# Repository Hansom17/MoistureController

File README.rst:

.. zephyr:code-sample:: moisture-controller
   :name: Moisture Controller

   Print "Hello World" to the console.

Overview
********

A simple sample that can be used with any :ref:`supported board <boards>` and
prints "Hello World" to the console.

Building and Running
********************

This application can be built and executed on QEMU as follows:

.. zephyr-app-commands::
   :zephyr-app: samples/hello_world
   :host-os: unix
   :board: qemu_x86
   :goals: run
   :compact:

To build for another board, change "qemu_x86" above to that board's name.

Sample Output
=============

.. code-block:: console

    Hello World! x86

Exit QEMU by pressing :kbd:`CTRL+A` :kbd:`x`.

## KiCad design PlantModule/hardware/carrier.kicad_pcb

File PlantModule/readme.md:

# PlantModule

Plant device: an ESP32-C6 Zigbee end device, always awake for now (low power comes later). Design: [`specs.md`](specs.md).

```
firmware/    ESP-IDF project (build and flash: see below): main/, components/{mc_core,mc_hal,mc_zigbee}; host tests in firmware/test
hardware/    KiCad carrier board for the Waveshare ESP32-C6-Zero (specs.md Part C)
interface.yaml   the Zigbee interface definition (source for firmware header, converter and hub models)
scripts/     qr_png.swift (QR image for labels); the provisioning/label tool (make_label.py) is to be written
```

**State:** carrier board v1 is built and in hand; the firmware (host-tested core, hardware layer, esp-zigbee-sdk layer) builds, runs on the bench module and works with Zigbee2MQTT and the gateway (join, configuration, readings, watering, battery detection). Not done: provisioning (`make_label.py`, factory data, install codes), low power, a real battery cell test. The previous Zephyr/WiFi/MQTT/BLE firmware and its tests were removed and are in git history at commit `eb97b07`.

## Hardware

Regenerate and order from `hardware/`: `gen_sch.py` (schematic), `gen_pcb.py` (needs KiCad's bundled Python), `jlc_export.py` (JLCPCB files). `design.py` is the single source. Details and status in Part C of the spec.

## Build and flash the firmware

Needs **ESP-IDF v6.0.2** (installed with Espressif's installer; `~/.espressif/v6.0.2`), a USB cable to the module's USB-C port and, to see anything useful, a Zigbee coordinator with Zigbee2MQTT (the gateway, or `Gateway/scripts/bench.sh`).

### 1. Set up the shell (once per terminal)

```bash
source ~/.espressif/tools/activate_idf_v6.0.2.sh
cd PlantModule/firmware
```

### 2. Build

For a **bench module** (no factory data yet: it runs as the `carrier-v1` board and joins with the default Zigbee link key):

```bash
rm -f sdkconfig        # only when you switch between a bench and a release configuration
idf.py -DSDKCONFIG_DEFAULTS="sdkconfig.defaults;sdkconfig.dev" build
```

For a **release build** (no dev options; a module without valid factory data then enters safe mode, which is intended):

```bash
idf.py build
```

The target (ESP32-C6) is in `sdkconfig.defaults`, no `set-target` is needed. The first build downloads the Zigbee components (`espressif/esp-zigbee-lib`, `esp-zboss-lib`, pinned in `dependencies.lock`). Other options are in `idf.py menuconfig` under "PlantModule" and "PlantModule Zigbee": the development board and join flag, `CONFIG_MC_ZB_TX_POWER` (default 10 dBm) and `CONFIG_MC_ZIGBEE_STUB` (log instead of radio, for bench tests without a coordinator).

If the build stops with "build log version is too new" or a `build.ninja` error, the `build/` folder came from another ninja version: `idf.py fullclean`, then build again.

### 3. Find the module's port

```bash
ls /dev/cu.usb*          # macOS; Linux: ls /dev/ttyACM*
```

The ESP32-C6 shows up as `usbmodem…` (macOS) or `ttyACM…` (Linux). A Zigbee dongle shows up as `usbserial…`: do **not** flash that. The name changes when you use another USB port.

### 4. Flash

```bash
idf.py -p /dev/cu.usbmodem1101 flash
```

That writes the bootloader, the partition table and the app and **keeps the settings and the Zigbee network** (NVS and `zb_storage` are not touched). For a faster app-only update:

```bash
python -m esptool --port /dev/cu.usbmodem1101 write-flash 0x20000 build/plantmodule.bin
```

### Flashing all partitions (a new module, or a clean start)

`idf.py flash` writes the bootloader, the partition table, OTA data and the app. The **data partitions** are not written: `nvs` (settings, counters), `factory` (board name, serial, install code) and the Zigbee storage `zb_storage`/`zb_fct`. The layout is in `firmware/partitions.csv`:

| Partition | Offset | Size | Written by |
|---|---|---|---|
| bootloader | `0x0` | | `idf.py flash` |
| partition table | `0x8000` | | `idf.py flash` |
| `nvs` | `0x9000` | `0x6000` | the firmware at run time |
| `otadata` | `0xf000` | `0x2000` | `idf.py flash` |
| `phy_init` | `0x11000` | `0x1000` | the firmware at run time |
| `factory` | `0x12000` | `0x1000` | **`scripts/factory_image.py`, below** |
| `zb_storage`, `zb_fct` | `0x13000`, `0x17000` | `0x4000`, `0x1000` | the Zigbee stack at run time |
| `ota_0` (the app) | `0x20000` | `0x1a0000` | `idf.py flash` |

**A module from scratch** (all partitions, including the factory data):

```bash
python -m esptool --port /dev/cu.usbmodem1101 erase-flash                      # wipes everything, also the factory data
../scripts/factory_image.py --board carrier-v1 --serial MC000001 --out factory.bin
idf.py -p /dev/cu.usbmodem1101 flash                                           # bootloader, table, otadata, app
python -m esptool --port /dev/cu.usbmodem1101 write-flash 0x12000 factory.bin # the factory partition
```

`scripts/factory_image.py` builds the 4 KB image of the `factory` partition (layout in `specs.md` §10 and `mc_factory.h`; the C parser accepts what it writes). Add `--install-code <32 hex characters>` for a module that must use an install code and `--require-install-code` so that it refuses to join without one. Keep the install code and the image out of git: the code is a secret, and the gateway needs the same code to accept the module.

Without factory data a module enters safe mode (`factory_invalid`), unless it is a bench build (`sdkconfig.dev`), which runs as `carrier-v1`. A module with factory data is not touched by a normal `idf.py flash`, and a factory reset (10 s button) keeps it.

**One file** (for a production line, or to flash from another machine that has no ESP-IDF):

```bash
idf.py merge-bin                       # build/merged-binary.bin: bootloader, table, otadata and app in one image
python -m esptool --port /dev/cu.usbmodem1101 write-flash 0x0 build/merged-binary.bin
python -m esptool --port /dev/cu.usbmodem1101 write-flash 0x12000 factory.bin     # then the factory data
```

The merged image **fills the gaps between its parts with `0xFF`**, so writing it also **erases `nvs`, `factory` and the Zigbee storage**: the module forgets its settings and its network, and the factory data must be written again afterwards (the last line). Use it only for a clean start, never as an update of a module in use.

### 5. Look at the log

```bash
idf.py -p /dev/cu.usbmodem1101 monitor     # Ctrl+] leaves
```

**Opening the USB port of the C6 resets the module** (most serial tools do). That is harmless, but a module that is working would restart and rejoin. The log shows `boot reason`, `stack ready, joined` or `factory new`, and the Zigbee signals.

### 6. Join the module to the gateway

1. Open the join window (app: **Devices → Add device**).
2. A module that has never joined starts looking for a network by itself (fast LED blink, about three minutes). One that belonged to another network: **hold the button for 10 seconds** (factory reset), it restarts and looks for a network. A short press only identifies it (LED blinks); a 3 s hold starts a search when it is not joined.
3. The module appears in the app (joined, interview, configure, ready); set its slots in **Edit configuration**.

### Changing the attribute set

Adding, removing or re-ordering attributes in `interface.yaml` (or editing its `reporting` table) needs **no erase and no new join**. The Zigbee stack keeps its reporting records in `zb_storage` and with records left over from a different attribute set it aborts at the first report (`zb_assert`). So the firmware hashes what it registers and remembers the hash in NVS (`mc_zb/attr_hash`). On the first start after a change it throws the stored records away and sets up its own from the `reporting` table (log line `attribute set changed: reporting records rebuilt`); the network, the bindings and the settings stay. A module without a network just stores the new hash. Flash the app only (`write-flash 0x20000 build/plantmodule.bin`) and the module comes back on its own.

The Zigbee storage still has to be erased for a module whose network is gone (new coordinator) or to start from scratch:

```bash
python -m esptool --port /dev/cu.usbmodem1101 erase-region 0x9000 0x6000     # NVS: settings, counters, "has booted" flag
python -m esptool --port /dev/cu.usbmodem1101 erase-region 0x13000 0x5000    # Zigbee storage and its factory-test partition
```

Then open the join window, wait for the module, and the gateway's configure step runs again.

### Changing a value of the interface

Values in `interface.yaml` (ranges, defaults, battery tunables) are compiled into the firmware; after editing it regenerate and rebuild:

```bash
python3 scripts/gen_interface_h.py && python3 ../Gateway/scripts/gen_converter.py && python3 ../Gateway/scripts/gen_hub_params.py
```

Not everything needs a flash: the table in `specs.md` §6.1 shows for each battery setting whether the module, the hub or both use it. Hub-only values (the percentage curve) need only the regenerate step and a hub restart; thresholds and calibration are set from the app and need no rebuild.

### Tests (no hardware, no ESP-IDF)

```bash
scripts/test_host.sh       # generated files are current, then the 127 host tests with ASan/UBSan
```

CI runs this on every pull request and also builds the firmware for the ESP32-C6 (`firmware-build` job in `.github/workflows/ci.yml`).

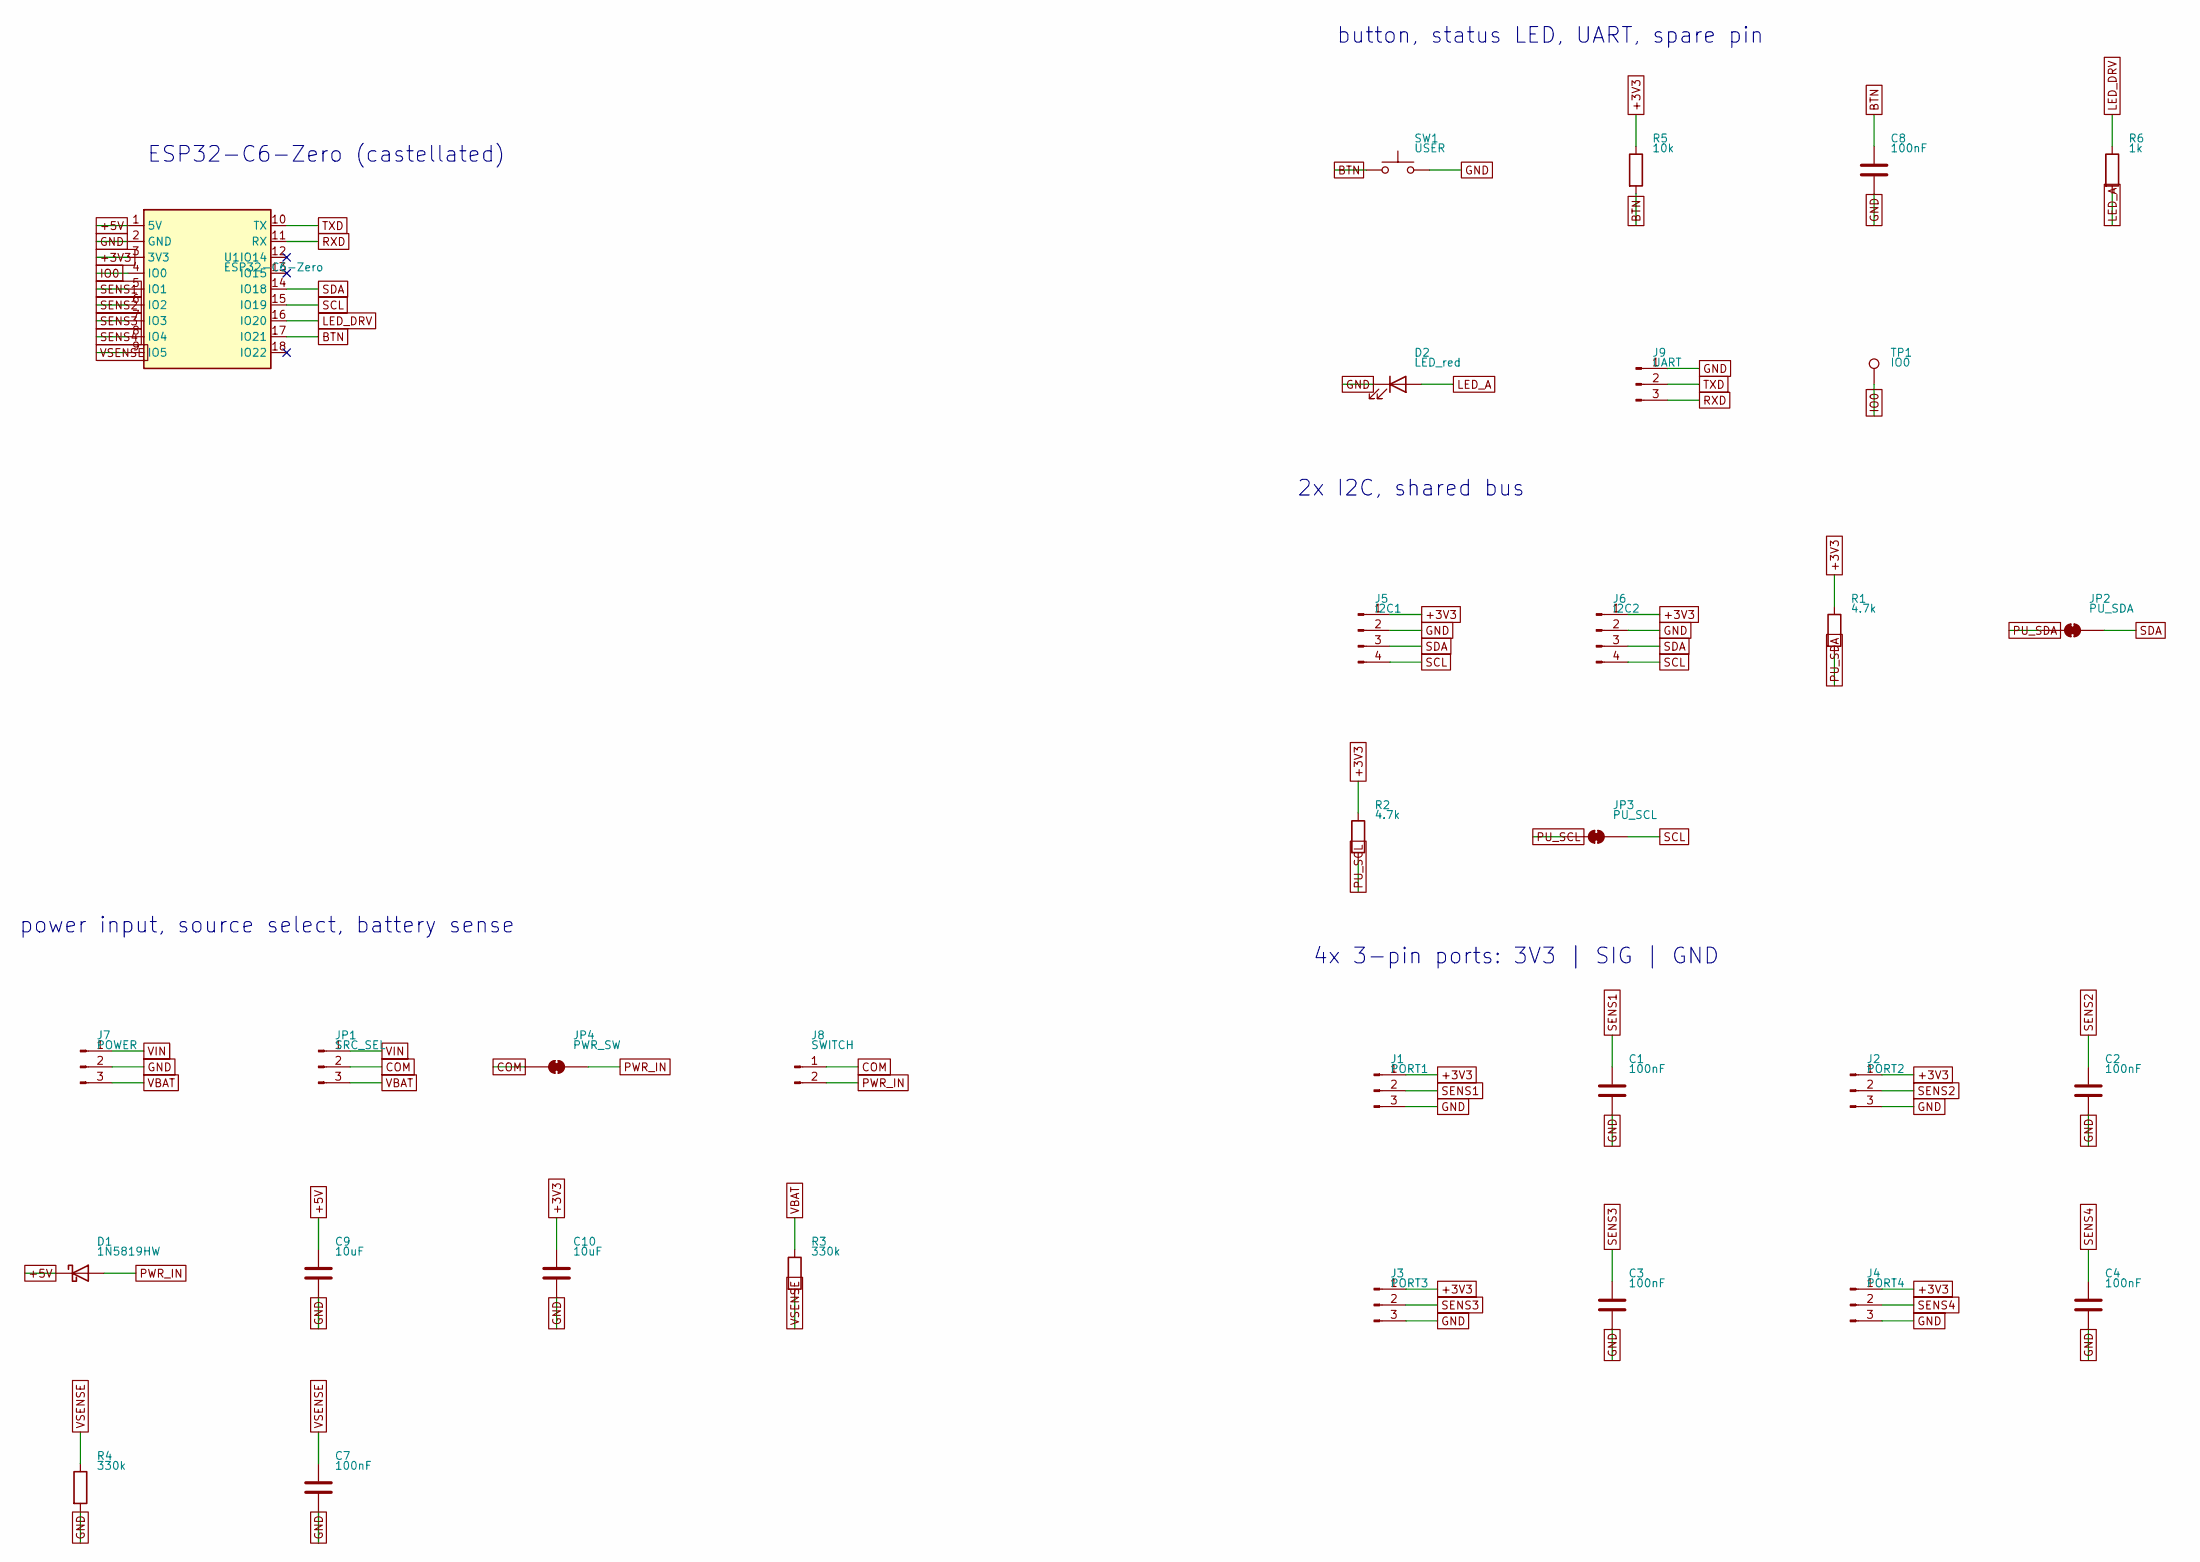
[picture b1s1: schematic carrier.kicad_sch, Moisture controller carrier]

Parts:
C1, C2, C3, C4, C7, C8: 100nF; C_0603_1608Metric
C9, C10: 10uF; C_0805_2012Metric
D1: 1N5819HW; D_SOD-123
D2: LED_red; LED_0603_1608Metric
J1: PORT1; JST_XH_B3B-XH-A_1x03_P2.50mm_Vertical
J2: PORT2; JST_XH_B3B-XH-A_1x03_P2.50mm_Vertical
J3: PORT3; JST_XH_B3B-XH-A_1x03_P2.50mm_Vertical
J4: PORT4; JST_XH_B3B-XH-A_1x03_P2.50mm_Vertical
J5: I2C1; JST_XH_B4B-XH-A_1x04_P2.50mm_Vertical
J6: I2C2; JST_XH_B4B-XH-A_1x04_P2.50mm_Vertical
J7: POWER; JST_XH_B3B-XH-A_1x03_P2.50mm_Vertical
J8: SWITCH; PinHeader_1x02_P2.54mm_Vertical
J9: UART; PinHeader_1x03_P2.54mm_Vertical
JP1: SRC_SEL; PinHeader_1x03_P2.54mm_Vertical
JP2: PU_SDA; SolderJumper-2_P1.3mm_Bridged_RoundedPad1.0x1.5mm
JP3: PU_SCL; SolderJumper-2_P1.3mm_Bridged_RoundedPad1.0x1.5mm
JP4: PWR_SW; SolderJumper-2_P1.3mm_Bridged_RoundedPad1.0x1.5mm
R1, R2: 4.7k; R_0603_1608Metric
R3, R4: 330k; R_0603_1608Metric
R5: 10k; R_0603_1608Metric
R6: 1k; R_0603_1608Metric
SW1: USER; SW_Push_1P1T_NO_CK_KMR2
TP1: IO0; TestPoint_Pad_D1.5mm
U1: ESP32-C6-Zero

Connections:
+3V3: C10.1, J1.1, J2.1, J3.1, J4.1, J5.1, J6.1, R1.1, R2.1, R5.1, U1.3 (3V3)
+5V: C9.1, D1.1 (K), U1.1 (5V)
BTN: C8.1, R5.2, SW1.1, U1.17 (IO21)
COM: J8.1, JP1.2, JP4.1 (A)
GND: C1.2, C2.2, C3.2, C4.2, C7.2, C8.2, C9.2, C10.2, D2.1 (K), J1.3, J2.3, J3.3, J4.3, J5.2, J6.2, J7.2, J9.1, R4.2, SW1.2, U1.2 (GND)
IO0: TP1.1 (1_1), U1.4 (IO0)
LED_A: D2.2 (A), R6.2
LED_DRV: R6.1, U1.16 (IO20)
PU_SCL: JP3.1 (A), R2.2
PU_SDA: JP2.1 (A), R1.2
PWR_IN: D1.2 (A), J8.2, JP4.2 (B)
RXD: J9.3, U1.11 (RX)
SCL: J5.4, J6.4, JP3.2 (B), U1.15 (IO19)
SDA: J5.3, J6.3, JP2.2 (B), U1.14 (IO18)
SENS1: C1.1, J1.2, U1.5 (IO1)
SENS2: C2.1, J2.2, U1.6 (IO2)
SENS3: C3.1, J3.2, U1.7 (IO3)
SENS4: C4.1, J4.2, U1.8 (IO4)
TXD: J9.2, U1.10 (TX)
VBAT: J7.3, JP1.3, R3.1
VIN: J7.1, JP1.1
VSENSE: C7.1, R3.2, R4.1, U1.9 (IO5)

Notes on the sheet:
button, status LED, UART, spare pin
ESP32-C6-Zero (castellated)
power input, source select, battery sense
2x I2C, shared bus
4x 3-pin ports: 3V3 | SIG | GND

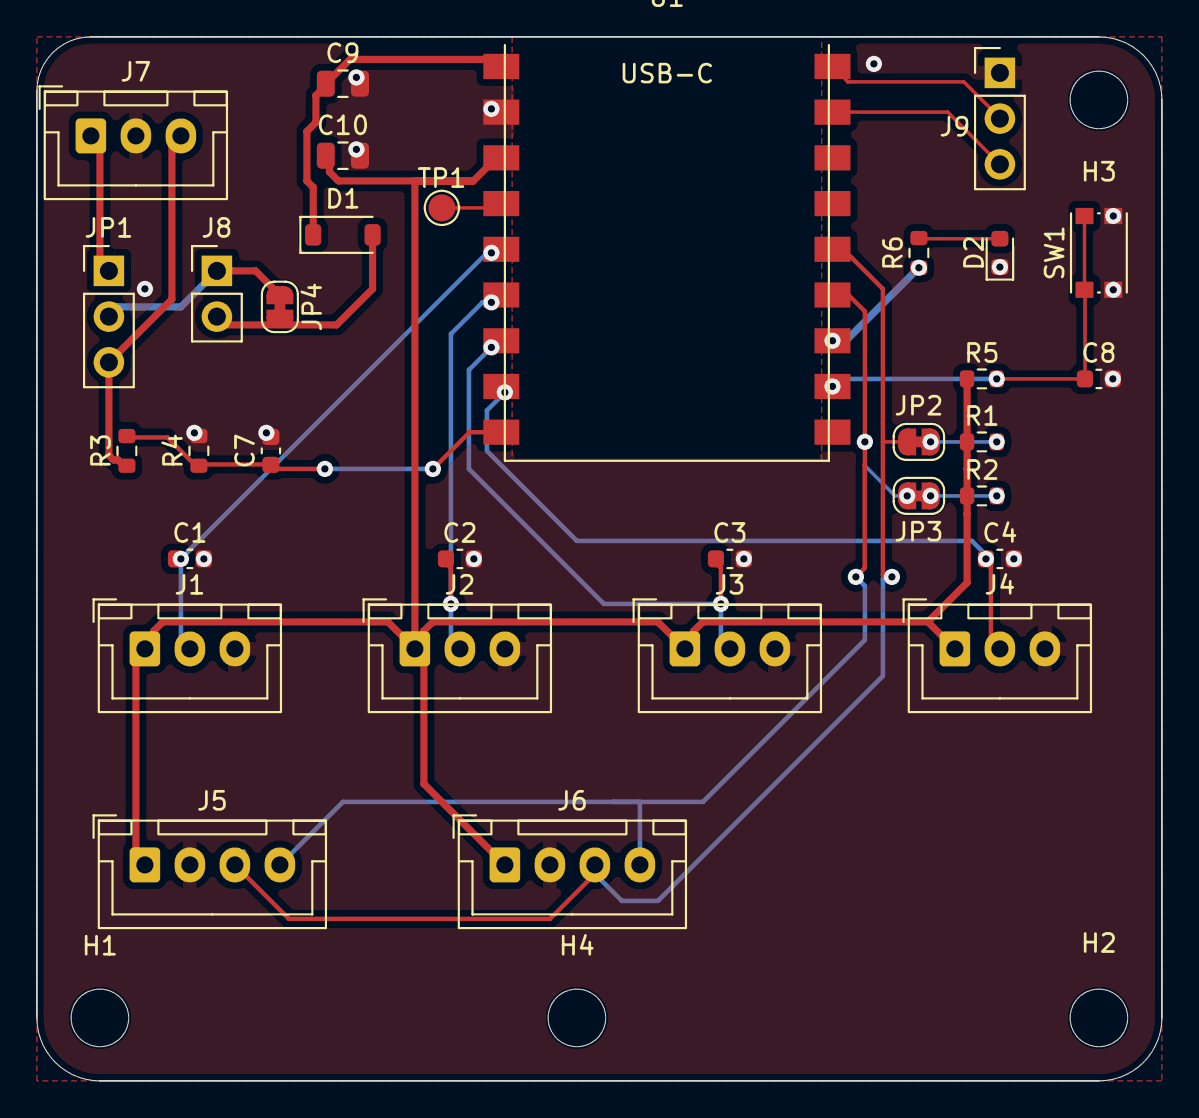
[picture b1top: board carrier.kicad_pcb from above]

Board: 2 copper layers, 62.5 x 58.0 mm, 36 parts (0 on the bottom side), 22 nets.

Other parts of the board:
H1, H2, H3, H4: M3; MountingHole_3.2mm_M3

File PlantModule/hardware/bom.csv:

"Refs","Value","Footprint","Qty"
"C1-C4,C7,C8","100nF","Capacitor_SMD:C_0603_1608Metric","6"
"C9,C10","10uF","Capacitor_SMD:C_0805_2012Metric","2"
"D1","B5819W","Diode_SMD:D_SOD-123","1"
"D2","STATUS","LED_SMD:LED_0603_1608Metric","1"
"J1","PORT1","Connector_JST:JST_XH_B3B-XH-A_1x03_P2.50mm_Vertical","1"
"J2","PORT2","Connector_JST:JST_XH_B3B-XH-A_1x03_P2.50mm_Vertical","1"
"J3","PORT3","Connector_JST:JST_XH_B3B-XH-A_1x03_P2.50mm_Vertical","1"
"J4","PORT4","Connector_JST:JST_XH_B3B-XH-A_1x03_P2.50mm_Vertical","1"
"J5","I2C1","Connector_JST:JST_XH_B4B-XH-A_1x04_P2.50mm_Vertical","1"
"J6","I2C2","Connector_JST:JST_XH_B4B-XH-A_1x04_P2.50mm_Vertical","1"
"J7","POWER","Connector_JST:JST_XH_B3B-XH-A_1x03_P2.50mm_Vertical","1"
"J8","SWITCH","Connector_PinHeader_2.54mm:PinHeader_1x02_P2.54mm_Vertical","1"
"J9","UART","Connector_PinHeader_2.54mm:PinHeader_1x03_P2.54mm_Vertical","1"
"JP1","SRC_SEL","Connector_PinHeader_2.54mm:PinHeader_1x03_P2.54mm_Vertical","1"
"R1,R2","4.7k","Resistor_SMD:R_0603_1608Metric","2"
"R3,R4","330k","Resistor_SMD:R_0603_1608Metric","2"
"R5","10k","Resistor_SMD:R_0603_1608Metric","1"
"R6","1k","Resistor_SMD:R_0603_1608Metric","1"
"SW1","USER","Button_Switch_SMD:SW_Push_1P1T_NO_CK_KMR2","1"
"U1","ESP32-C6-Zero","carrier:ESP32-C6-Zero","1"
